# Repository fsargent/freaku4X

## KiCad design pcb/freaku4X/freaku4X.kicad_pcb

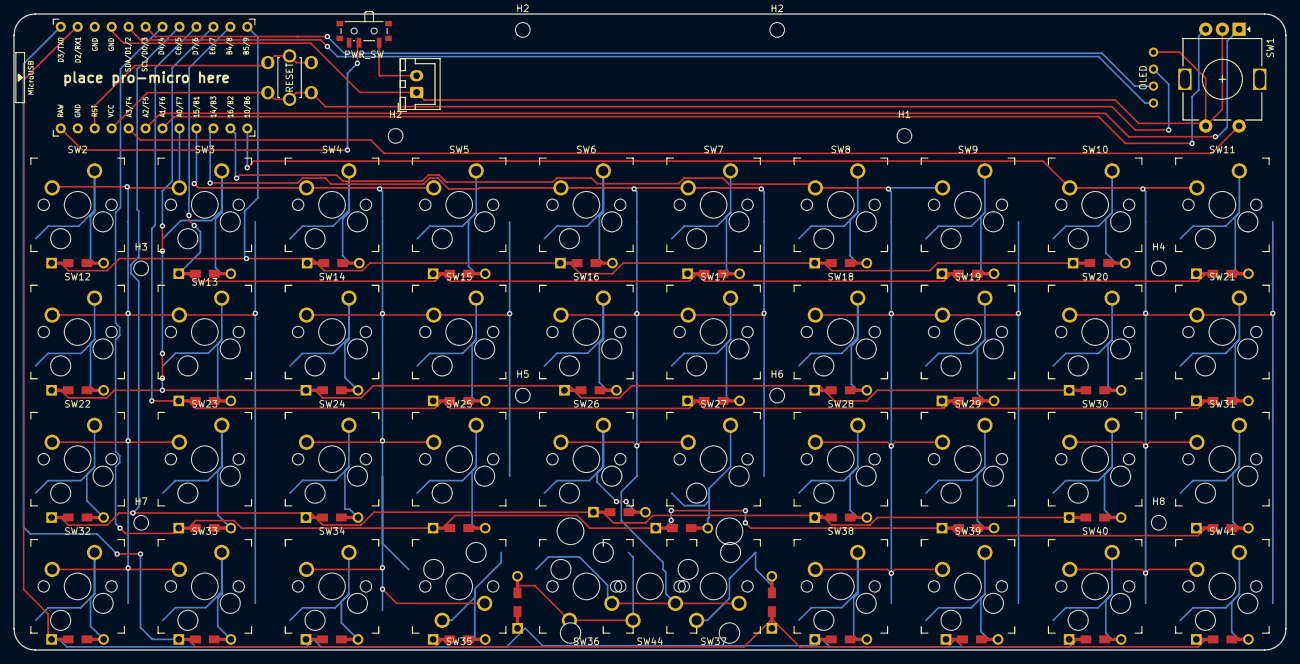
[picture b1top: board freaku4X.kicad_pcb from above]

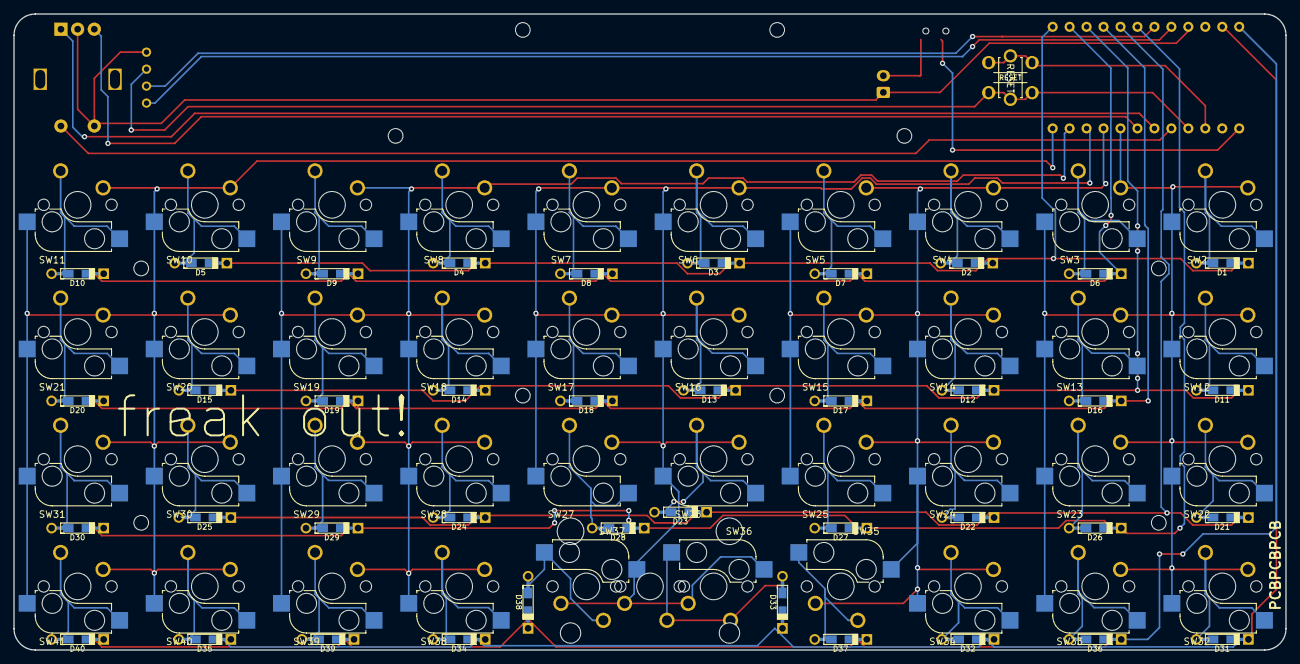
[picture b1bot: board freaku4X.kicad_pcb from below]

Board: 2 copper layers, 190.5 x 95.2 mm, 97 parts (41 on the bottom side), 62 nets.

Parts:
D1, D2, D3, D4, D5, D6, D7, D8, D9, D10, D11, D12, D13, D14, D15, D16, D17, D18, D19, D20, D21, D22, D23, D24, D25, D26, D27, D28, D29, D30, D31, D32, D33, D34, D35, D36, D37, D38, D39, D40: 1N4148; Diode-dual
H1, H2, H2#2, H2#3, H3, H4, H5, H6, H7, H8: MountingHole; MountingHole_2.2mm_M2
OL1: OLED; OLED_v2
PWR_SW: SW_SPDT_PCM12
SW1: RotaryEncoder_Switch; RotaryEncoder_Alps_EC11E-Switch_Vertical_H20mm
SW2, SW3, SW4, SW5, SW6, SW7, SW8, SW9, SW10, SW11, SW12, SW13, SW14, SW15, SW16, SW17, SW18, SW19, SW20, SW21, SW22, SW23, SW24, SW25, SW26, SW27, SW28, SW29, SW30, SW31, SW32, SW33, SW34, SW35, SW36, SW37, SW38, SW39, SW40, SW41: SW_SPST; Kailh_socket_MX_optional
SW42: SW_SPST; ResetSW_4
SW43: SW_SPST; ResetSW
SW44: SW_SPST; SW_MX
U1: ProMicro; ProMicro_v3

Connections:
unnamed: D1.2 (A), SW2.1 (A)
unnamed: D2.2 (A), SW4.1 (A)
unnamed: D3.2 (A), SW6.1 (A)
unnamed: D4.2 (A), SW8.1 (A)
unnamed: D5.2 (A), SW10.1 (A)
unnamed: D6.2 (A), SW3.1 (A)
unnamed: D7.2 (A), SW5.1 (A)
unnamed: D8.2 (A), SW7.1 (A)
unnamed: D9.2 (A), SW9.1 (A)
unnamed: D10.2 (A), SW11.1 (A)
unnamed: D11.2 (A), SW12.1 (A)
unnamed: D12.2 (A), SW14.1 (A)
unnamed: D13.2 (A), SW16.1 (A)
unnamed: D14.2 (A), SW18.1 (A)
unnamed: D15.2 (A), SW20.1 (A)
unnamed: D16.2 (A), SW13.1 (A)
unnamed: D17.2 (A), SW15.1 (A)
unnamed: D18.2 (A), SW17.1 (A)
unnamed: D19.2 (A), SW19.1 (A)
unnamed: D20.2 (A), SW21.1 (A)
unnamed: D21.2 (A), SW22.1 (A)
unnamed: D22.2 (A), SW24.1 (A)
unnamed: D23.2 (A), SW26.1 (A)
unnamed: D24.2 (A), SW28.1 (A)
unnamed: D25.2 (A), SW30.1 (A)
unnamed: D26.2 (A), SW23.1 (A)
unnamed: D27.2 (A), SW25.1 (A)
unnamed: D28.2 (A), SW27.1 (A)
unnamed: D29.2 (A), SW29.1 (A)
unnamed: D30.2 (A), SW31.1 (A)
unnamed: D31.2 (A), SW32.1 (A)
unnamed: D32.2 (A), SW34.1 (A)
unnamed: D33.2 (A), SW36.1 (A), SW44.1 (A)
unnamed: D34.2 (A), SW38.1 (A)
unnamed: D35.2 (A), SW40.1 (A)
unnamed: D36.2 (A), SW33.1 (A)
unnamed: D37.2 (A), SW35.1 (A)
unnamed: D38.2 (A), SW37.1 (A)
unnamed: D39.2 (A), SW39.1 (A)
unnamed: D40.2 (A), SW41.1 (A)
col1: SW2.2 (B), SW3.2 (B), SW12.2 (B), SW13.2 (B), SW22.2 (B), SW23.2 (B), SW32.2 (B), SW33.2 (B), U1.17 (A0/PF7)
col2: SW4.2 (B), SW5.2 (B), SW14.2 (B), SW15.2 (B), SW24.2 (B), SW25.2 (B), SW34.2 (B), SW35.2 (B), U1.16 (15/PB1)
col3: SW6.2 (B), SW7.2 (B), SW16.2 (B), SW17.2 (B), SW26.2 (B), SW27.2 (B), SW36.2 (B), SW37.2 (B), SW44.2 (B), U1.15 (14/PB3)
col4: SW8.2 (B), SW9.2 (B), SW18.2 (B), SW19.2 (B), SW28.2 (B), SW29.2 (B), SW38.2 (B), SW39.2 (B), U1.14 (16/PB2)
col5: SW10.2 (B), SW11.2 (B), SW20.2 (B), SW21.2 (B), SW30.2 (B), SW31.2 (B), SW40.2 (B), SW41.2 (B), U1.13 (10/PB6)
encoder_switch: SW1.S2, U1.20 (A3/PF4)
gnd: OL1.4 (GND), SW1.C, SW1.S1, U1.3 (GND), U1.4 (GND), U1.23 (GND)
padA: SW1.A, U1.19 (A2/PF5)
padB: SW1.B, U1.18 (A1/PF6)
raw: PWR_SW.2, U1.24 (RAW)
row1: D1.1 (K), D2.1 (K), D3.1 (K), D4.1 (K), D5.1 (K), U1.12 (9/PB5)
row2: D6.1 (K), D7.1 (K), D8.1 (K), D9.1 (K), D10.1 (K), U1.11 (8/PB4)
row3: D11.1 (K), D12.1 (K), D13.1 (K), D14.1 (K), D15.1 (K), U1.10 (7/PE6)
row4: D16.1 (K), D17.1 (K), D18.1 (K), D19.1 (K), D20.1 (K), U1.9 (6/PD7)
row5: D21.1 (K), D22.1 (K), D23.1 (K), D24.1 (K), D25.1 (K), U1.8 (5/PC6)
row6: D26.1 (K), D27.1 (K), D28.1 (K), D29.1 (K), D30.1 (K), U1.7 (4/PD4)
row7: D31.1 (K), D32.1 (K), D33.1 (K), D34.1 (K), D35.1 (K), U1.2 (RX1/PD2)
row8: D36.1 (K), D37.1 (K), D38.1 (K), D39.1 (K), D40.1 (K), U1.1 (TX0/PD3)
rst: SW42.2 (B), SW43.2 (B), U1.22 (RST)
scl: OL1.2 (SCL), U1.6 (3/PD0)
sda: OL1.1 (SDA), U1.5 (2/PD1)
vcc: OL1.3 (VCC), SW42.1 (A), SW43.1 (A), U1.21 (VCC)

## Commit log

2022-07-25 Add Battery and Switch for Nice!Nano
